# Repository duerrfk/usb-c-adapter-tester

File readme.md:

USB-C-Adapter-Tester is a device to test USB-C-to-USB-A/Micro-USB cables and adapters for conformity with the USB standard. Such USB-C adapters should use a 56k resistor connecting the 5 V line to the CC (Channel Configuration) line to signal to the downstream device (e.g., smartphone) that it should not draw more than standard USB power. However, some cables and adapters use smaller resistor values resulting in excessive current drawn by the downstream USB-C device, which might damage the upstream USB device providing power.

USB-C-Adapter-Tester consists of a hardware and a software part:

* circuit board (PCB) for connecting the USB-C cable/adapter under test 
* software based on the Arduino platform

Eagle files and PDFs for the hardware (schematics, board layout) can be found in folder `pcb`. The software can be found in folder `src`.

# Hardware

The tester hardware as depicted in the figures below consists of a microcontroller (Atmega 328p; same chip as the Arduino UNO) featuring an Analog-to-Digital Converter (ADC). The ADC measures the voltage drop along a 5.1k resistor (actually, two separate 5.1k resistors on different channels of the ADC since USB-C features two CC lines so you can plug-in the USB-C cable either way). Knowing the resistance and the voltage drop measured by the ADC, the microcontroller calculates the current (ICC) flowing on the CC line. If ICC is within the specified range (80 uA +- 20 % according to the standard), an LED signaling a "good" cable is turned on from an GPIO pin. If it is outside the range, another LED signaling a "bad" cable is turned on.

The cable to be checked is connected to an USB host or charger to power the microcontroller. The good old Atmega 328p can be powered from 5V, which is the voltage provided by standard USB-A and Micro-USB. 

Since the internal voltage reference of the Atmega might not be very precise, an external 2.5 V voltage reference diode is used as reference for the ADC. 

As soon as the cable under test is plugged in, the microcontroller starts measuring the voltage drop along the 5.1k resistor using the ADC, translates the voltage to current (R = V/I), compares the measured current to the allowed current range (80 uA +- 20 %), and switches on the corresponding "good" or "bad cable" LED.

# Programming the Microcontroller

The code is implemented for the Arduino platform. 

The device is programmed through an in-system programmer port (6 pin ISP) with the following standard layout:

    MISO <-- 1 2 --> VCC
     SCK <-- 3 4 --> MOSI
     RST <-- 5 6 --> GND

To prepare the Atmega, program the following fuses (note that "0" means 
that the fuse is programmed):

* CKSEL = 0010: use internal 8 MHz RC oscillator
* CKDIV8 = 1: 8 MHz system clock (do not divide the 8 MHz internal clock by 8)
* SPIEN = 0: enable serial programming
* BODLEVEL = 101: brown-out detection set to 2.7 V
* SUT = 00: lowest possible startup time (6 CK from power-down; since we use
  BOD, we do not need additional waiting time for the power source to come up)
    
Using avrdude, the command looks like this (you might need
to execute this command as root):

    $ avrdude -c usbasp -p m328p -U lfuse:w:0xc2:m -U hfuse:w:0xd9:m -U efuse:w:0x05:m

Make sure to compile your code for the correct board (Atmega 328p at 8 MHz). In the repository, 
you will find a suitable board definition for the Arduino IDE (see folder 
`board_definition`). Copy the directory `atmega328_8MHz` into the folder 
`hardware` in your Arduino sketchbook. Then you should find and select the 
board  called `ATmega328P @ 8 MHz` under the menu item `Tools/Board`. 

Compiling generates a hex file that you need to program the Atmega. This hex 
file is a little hidden in the temporary build directory of the Arduino
IDE. If you use Linux  and Arduino IDE 1.6, have a look at the `/tmp` 
directory. After hitting the  compile button in the Arduino IDE, search for the
latest hex file called `usb-c-adapter-tester.cpp.hex` in a temporary directory named `/tmp/build...`. If you have found the hex file, you can flash it using avrdude (again, you might need to be root):

    $ avrdude -p m328p -c usbasp -v -U flash:w:/tmp/build6535101126624677692.tmp/usb-c-adapter-tester.cpp.hex

# Licensing

USB-C-Adapter-Tester uses two licenses for open hardware and software, respectively:

* The software (source code) is licensed under the Apache License 2.0
* The hardware (schematic diagrams, circuit board layouts, hardware documentation) is licensed under the CERN Open Hardware Licence v1.2

Both licenses are included in the repository.

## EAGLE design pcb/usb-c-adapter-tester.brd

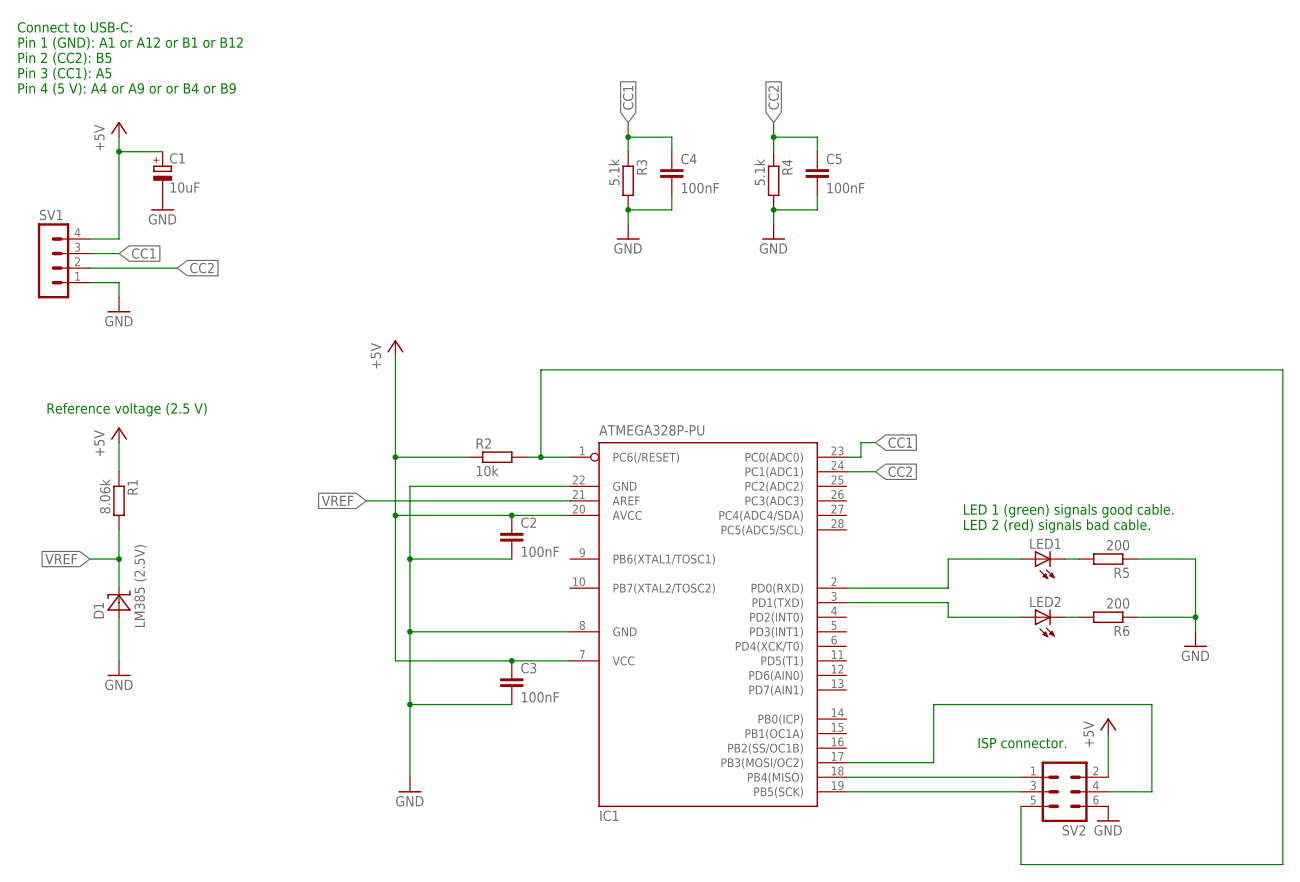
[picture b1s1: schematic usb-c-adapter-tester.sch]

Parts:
C1: 10uF; E2,5-5
C2, C3, C4, C5: 100nF; C050-024X044
D1: LM385 (2.5V); TO-92
IC1: ATMEGA328P-PU; DIL28-3
LED1, LED2: LED5MM
R1: 8.06k; 0207/7
R2: 10k; 0207/7
R3, R4: 5.1k; 0207/7
R5, R6: 200; 0207/7
SV1: MA04-1
SV2: MA03-2

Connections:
CC1: C4.1, IC1.23 (PC0(ADC0)), R3.1, SV1.3
CC2: C5.1, IC1.24 (PC1(ADC1)), R4.1, SV1.2
GND: C1.-, C2.2, C3.2, C4.2, C5.2, D1.+, IC1.8 (GND), IC1.22 (GND), R3.2, R4.2, R5.1, R6.1, SV1.1, SV2.6
unnamed: IC1.1 (PC6(/RESET)), R2.2, SV2.5
unnamed: LED1.K (C), R5.2
unnamed: LED2.K (C), R6.2
unnamed: IC1.17 (PB3(MOSI/OC2)), SV2.4
unnamed: IC1.2 (PD0(RXD)), LED1.A
unnamed: IC1.18 (PB4(MISO)), SV2.1
unnamed: IC1.3 (PD1(TXD)), LED2.A
unnamed: IC1.19 (PB5(SCK)), SV2.3
unnamed: C1.+, C2.1, C3.1, IC1.7 (VCC), IC1.20 (AVCC), R1.1, R2.1, SV1.4, SV2.2
VREF: D1.-, IC1.21 (AREF), R1.2

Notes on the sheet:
Connect to USB-C: Pin 1 (GND): A1 or A12 or B1 or B12 Pin 2 (CC2): B5 Pin 3 (CC1): A5 Pin 4 (5 V): A4 or A9 or or B4 or B9
LED 1 (green) signals good cable. LED 2 (red) signals bad cable.
ISP connector.
Reference voltage (2.5 V)

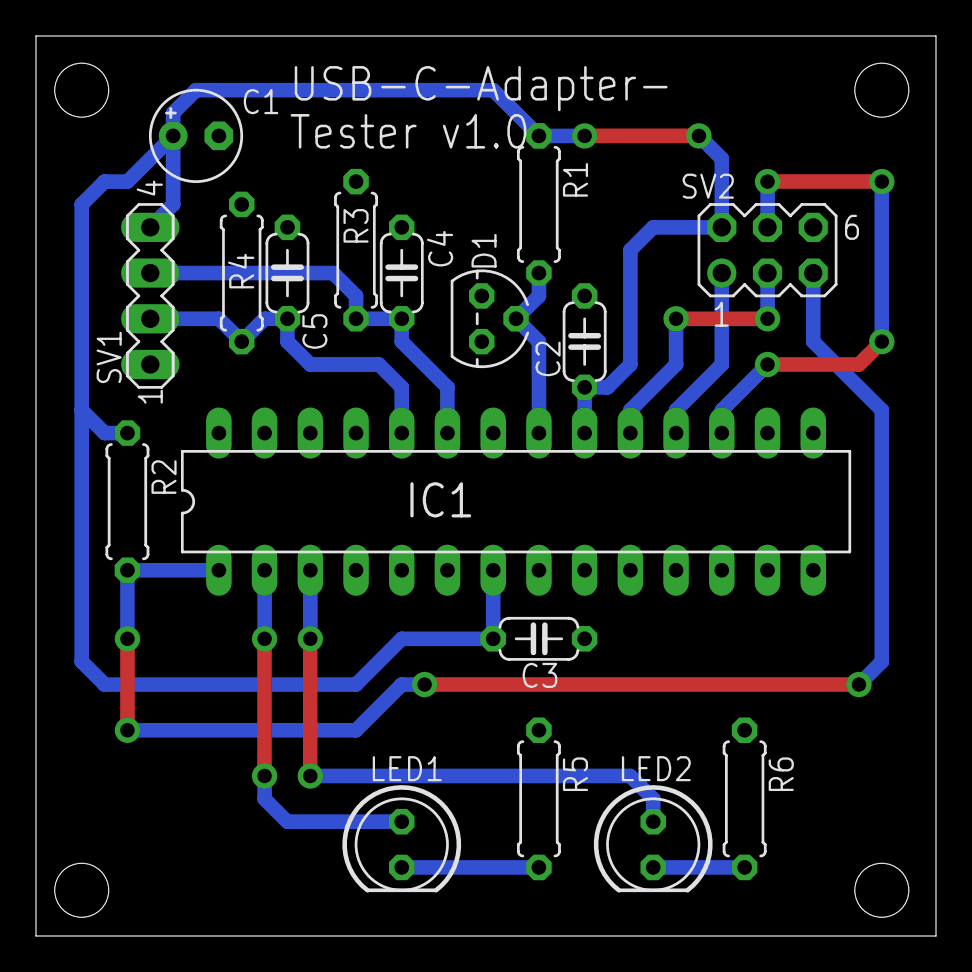
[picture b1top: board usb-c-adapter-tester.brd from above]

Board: 2 copper layers, 50.0 x 50.0 mm, 17 parts (0 on the bottom side), 13 nets.

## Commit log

2016-05-05 Initial check-in
2016-05-05 Updated readme file with licenses
2016-05-05 Added licenses
2016-05-05 Added licences
2016-05-05 Added license
2016-05-05 Changed board definition
2016-05-05 Added notice file
